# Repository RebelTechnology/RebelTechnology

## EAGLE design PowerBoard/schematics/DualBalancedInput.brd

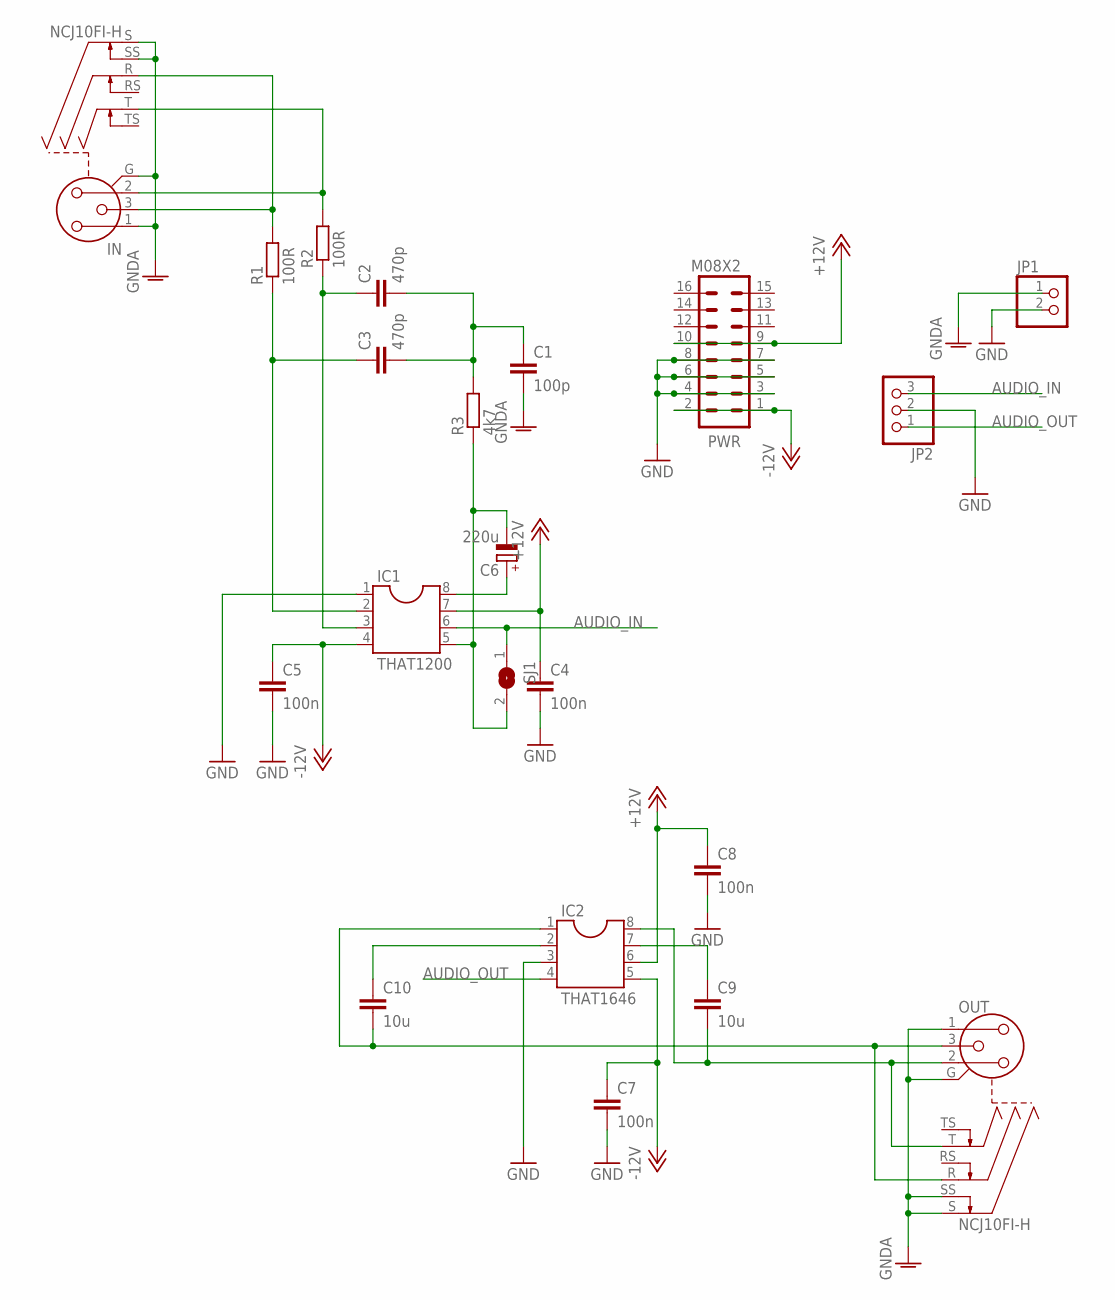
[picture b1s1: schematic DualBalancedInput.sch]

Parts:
C1: 100p; C050-025X075
C2, C3: 470p; C050-025X075
C4, C5, C7, C8: 100n; C050-025X075
C6: 220u; E5-8,5
C9, C10: 10u; C050-025X075
IC1: THAT1200; DIL08
IC2: THAT1646; DIL08
IN: NCJ10FI-H
JP1: PINHD-1X2; 1X02
JP2: PINHD-1X3; 1X03
OUT: NCJ10FI-H
PWR: M08X2; 2X8
R1, R2: 100R; 0207/7
R3: 4k7; 0207/7
SJ1: SJW

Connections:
+12V: C4.1, C8.1, IC1.7, IC2.6, PWR.9, PWR.10
-12V: C5.1, C7.1, IC1.4, IC2.5, PWR.1, PWR.2
AUDIO_IN: IC1.6, JP2.3, SJ1.1
AUDIO_OUT: IC2.4, JP2.1
GND: C4.2, C5.2, C7.2, C8.2, IC1.1, IC2.3, JP1.2, JP2.2, PWR.3, PWR.4, PWR.5, PWR.6, PWR.7, PWR.8
GNDA: C1.2, IN.1, IN.G, IN.S, IN.SS, JP1.1, OUT.1, OUT.G, OUT.S, OUT.SS
unnamed: C3.1, IC1.2, R1.1
unnamed: IN.3, IN.R, R1.2
unnamed: C2.1, IC1.3, R2.1
unnamed: IN.2, IN.T, R2.2
unnamed: C6.-, IC1.5, R3.1, SJ1.2
unnamed: C1.1, C2.2, C3.2, R3.2
unnamed: C9.1, IC2.7
unnamed: C10.1, IC2.2
unnamed: C6.+, IC1.8
unnamed: C9.2, IC2.8, OUT.2, OUT.T
unnamed: C10.2, IC2.1, OUT.3, OUT.R

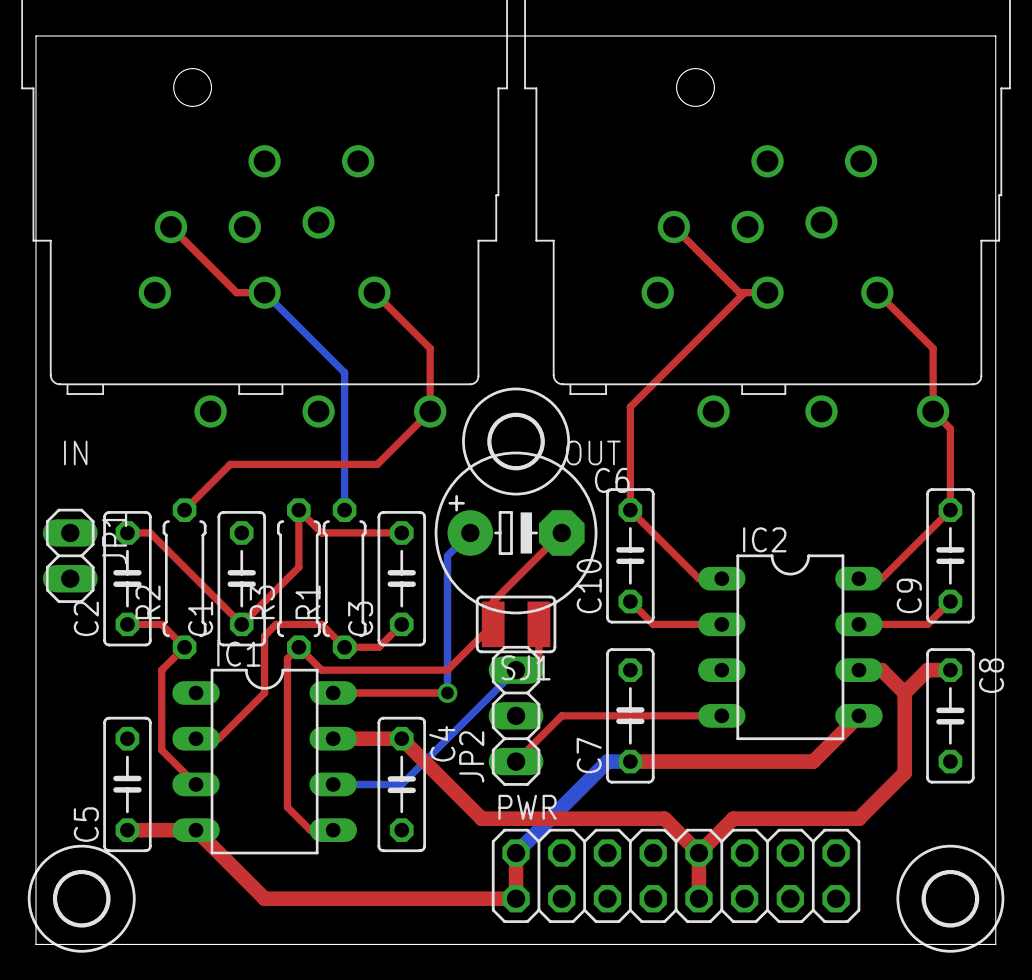
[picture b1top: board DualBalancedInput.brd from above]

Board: 2 copper layers, 53.3 x 50.5 mm, 24 parts (0 on the bottom side), 17 nets.

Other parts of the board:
U$1, U$2, U$3: 2,8

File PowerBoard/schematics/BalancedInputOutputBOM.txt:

Partlist exported from D:/Drive/Work/Rebel/ProjectFiles/RebelTechnology/PowerBoard/schematics/BalancedInputOutput.sch at 13/04/2015 14:58:14

Qty Value     Device          Package      Parts          Description                          
2             PINHD-1X2       1X02         JP1, JP3       PIN HEADER                           
1             PINHD-1X3       1X03         JP2            PIN HEADER                           
1             SJW             SJW          SJ1            SMD solder JUMPER                    
2   100R      R-EU_0207/7     0207/7       R1, R2         RESISTOR, European symbol            
4   100n      C-EU050-025X075 C050-025X075 C4, C5, C7, C8 CAPACITOR, European symbol           
1   100p      C-EU050-025X075 C050-025X075 C1             CAPACITOR, European symbol           
2   10u       C-EU050-025X075 C050-025X075 C9, C10        CAPACITOR, European symbol           
1   220u      CPOL-EUE5-8.5   E5-8,5       C6             POLARIZED CAPACITOR, European symbol 
2   470p      C-EU050-025X075 C050-025X075 C2, C3         CAPACITOR, European symbol           
1   4k7       R-EU_0207/7     0207/7       R3             RESISTOR, European symbol            
1   M08X2     M08X2           2X8          PWR                                                 
2   NCJ10FI-H NCJ10FI-H       NCJ10FI-H    IN, OUT        Neutrik Audio Connector XLR SERIES   
1   THAT1200  DIL8            DIL08        IC1            Dual In Line / Socket                
1   THAT1646  DIL8            DIL08        IC2            Dual In Line / Socket

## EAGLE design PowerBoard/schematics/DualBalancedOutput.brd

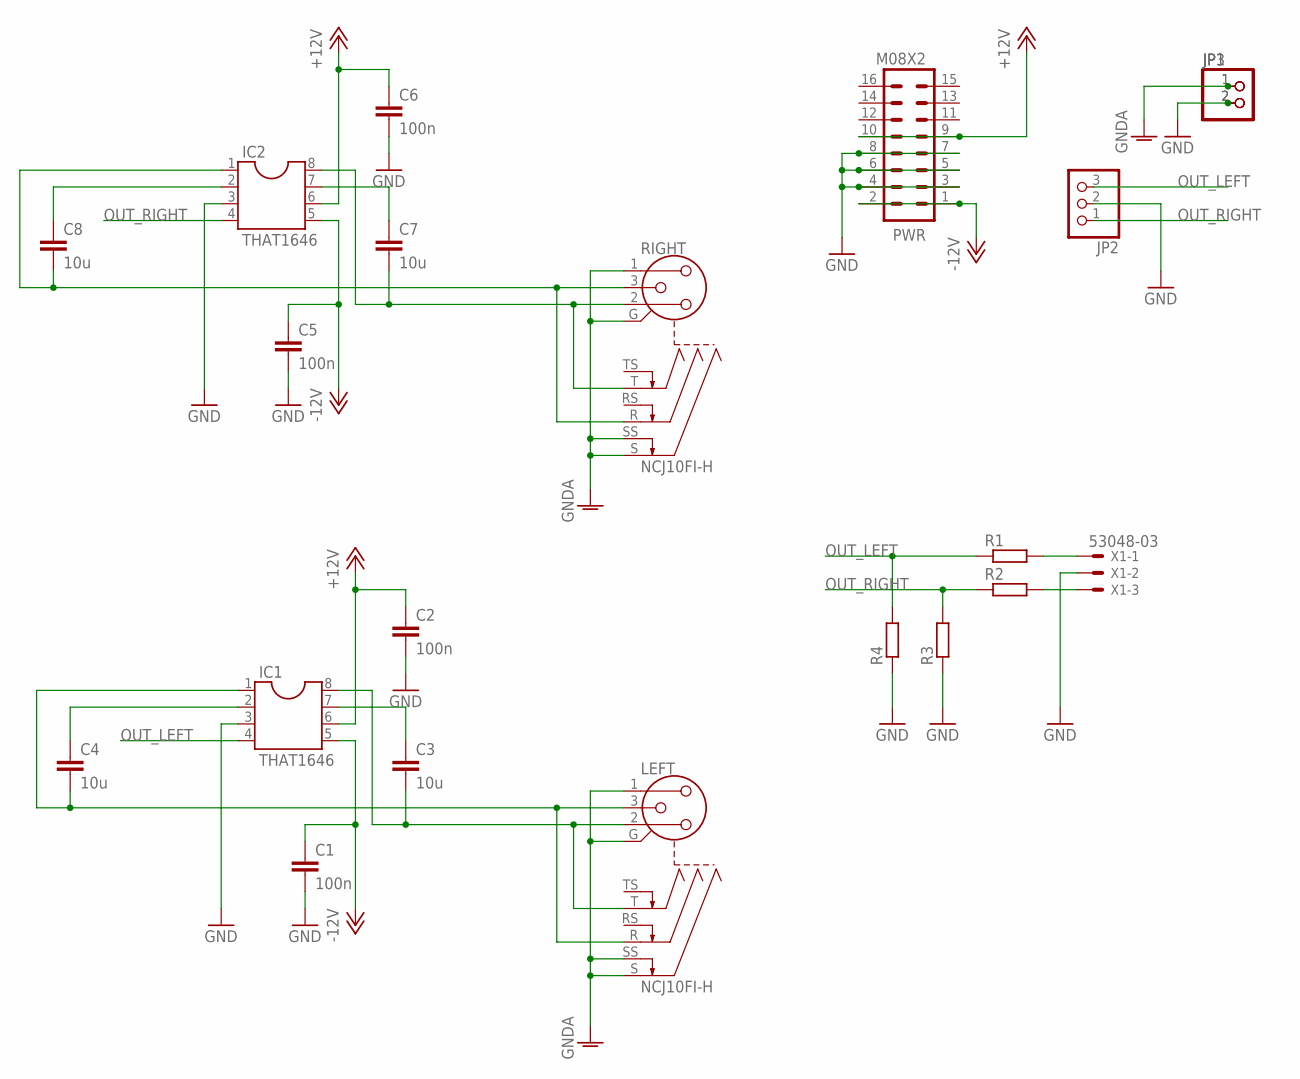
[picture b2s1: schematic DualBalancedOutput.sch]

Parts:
C1, C2, C5, C6: 100n; C050-025X075
C3, C4, C7, C8: 10u; C050-025X075
IC1, IC2: THAT1646; DIL08
JP1, JP3: PINHD-1X2; 1X02
JP2: PINHD-1X3; 1X03
LEFT: NCJ10FI-H
PWR: M08X2; 2X8
R1, R2, R3, R4: R-EU_0207/7; 0207/7
RIGHT: NCJ10FI-H
X1: 53048-03

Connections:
+12V: C2.1, C6.1, IC1.6, IC2.6, PWR.9, PWR.10
-12V: C1.1, C5.1, IC1.5, IC2.5, PWR.1, PWR.2
GND: C1.2, C2.2, C5.2, C6.2, IC1.3, IC2.3, JP1.2, JP2.2, JP3.2, PWR.3, PWR.4, PWR.5, PWR.6, PWR.7, PWR.8, R3.1, R4.1, X1.2
GNDA: JP1.1, JP3.1, LEFT.1, LEFT.G, LEFT.S, LEFT.SS, RIGHT.1, RIGHT.G, RIGHT.S, RIGHT.SS
unnamed: C3.2, IC1.8, LEFT.2, LEFT.T
unnamed: C4.2, IC1.1, LEFT.3, LEFT.R
unnamed: C3.1, IC1.7
unnamed: C4.1, IC1.2
unnamed: R2.2, X1.3
unnamed: C7.1, IC2.7
unnamed: R1.2, X1.1
unnamed: C8.1, IC2.2
unnamed: C7.2, IC2.8, RIGHT.2, RIGHT.T
unnamed: C8.2, IC2.1, RIGHT.3, RIGHT.R
OUT_LEFT: IC1.4, JP2.3, R1.1, R4.2
OUT_RIGHT: IC2.4, JP2.1, R2.1, R3.2

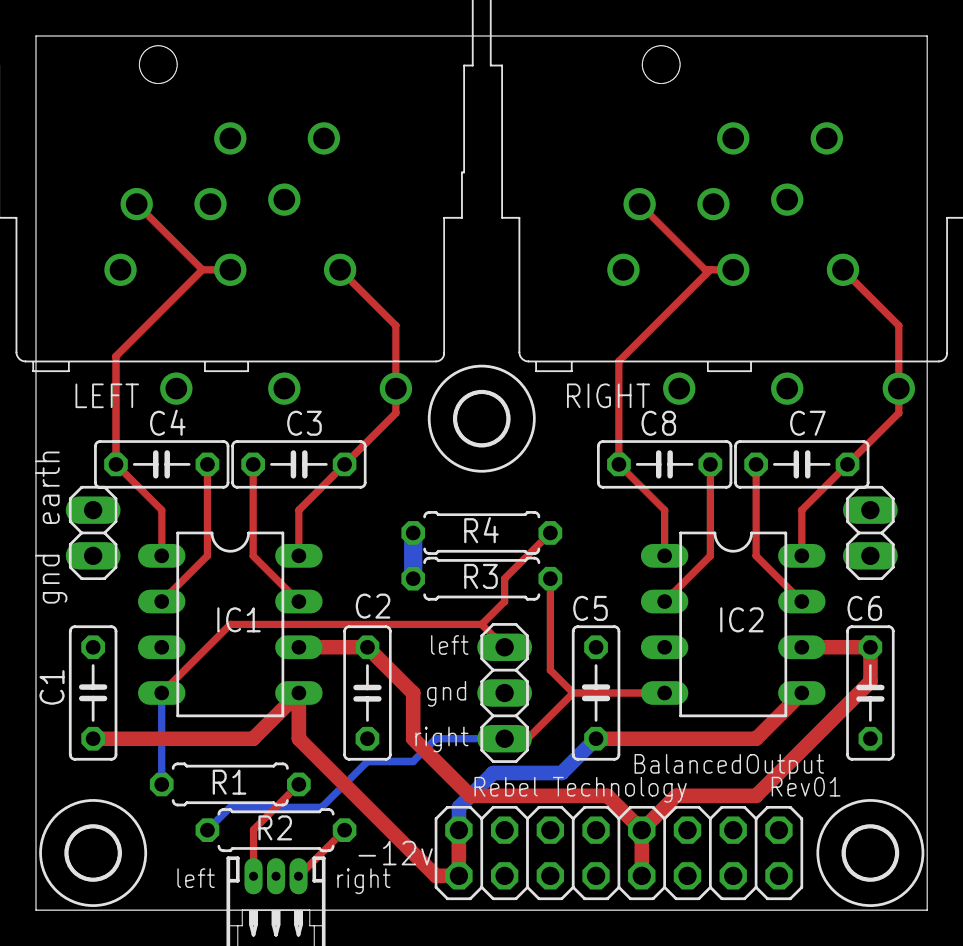
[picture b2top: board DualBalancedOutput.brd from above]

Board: 2 copper layers, 49.5 x 48.6 mm, 24 parts (0 on the bottom side), 16 nets.

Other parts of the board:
U$1, U$2, U$3: 2,8

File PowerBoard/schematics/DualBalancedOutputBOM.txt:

Partlist exported from D:/Drive/Work/Rebel/ProjectFiles/RebelTechnology/PowerBoard/schematics/DualBalancedOutput.sch at 13/04/2015 15:21:52

Qty Value     Device          Package      Parts          Description                        
2             PINHD-1X2       1X02         JP1, JP3       PIN HEADER                         
1             PINHD-1X3       1X03         JP2            PIN HEADER                         
4             R-EU_0207/7     0207/7       R1, R2, R3, R4 RESISTOR, European symbol          
4   100n      C-EU050-025X075 C050-025X075 C1, C2, C5, C6 CAPACITOR, European symbol         
4   10u       C-EU050-025X075 C050-025X075 C3, C4, C7, C8 CAPACITOR, European symbol         
1   53048-03  53048-03        53048-03     X1             CONNECTOR                          
1   M08X2     M08X2           2X8          PWR                                               
2   NCJ10FI-H NCJ10FI-H       NCJ10FI-H    LEFT, RIGHT    Neutrik Audio Connector XLR SERIES 
2   THAT1646  DIL8            DIL08        IC1, IC2       Dual In Line / Socket

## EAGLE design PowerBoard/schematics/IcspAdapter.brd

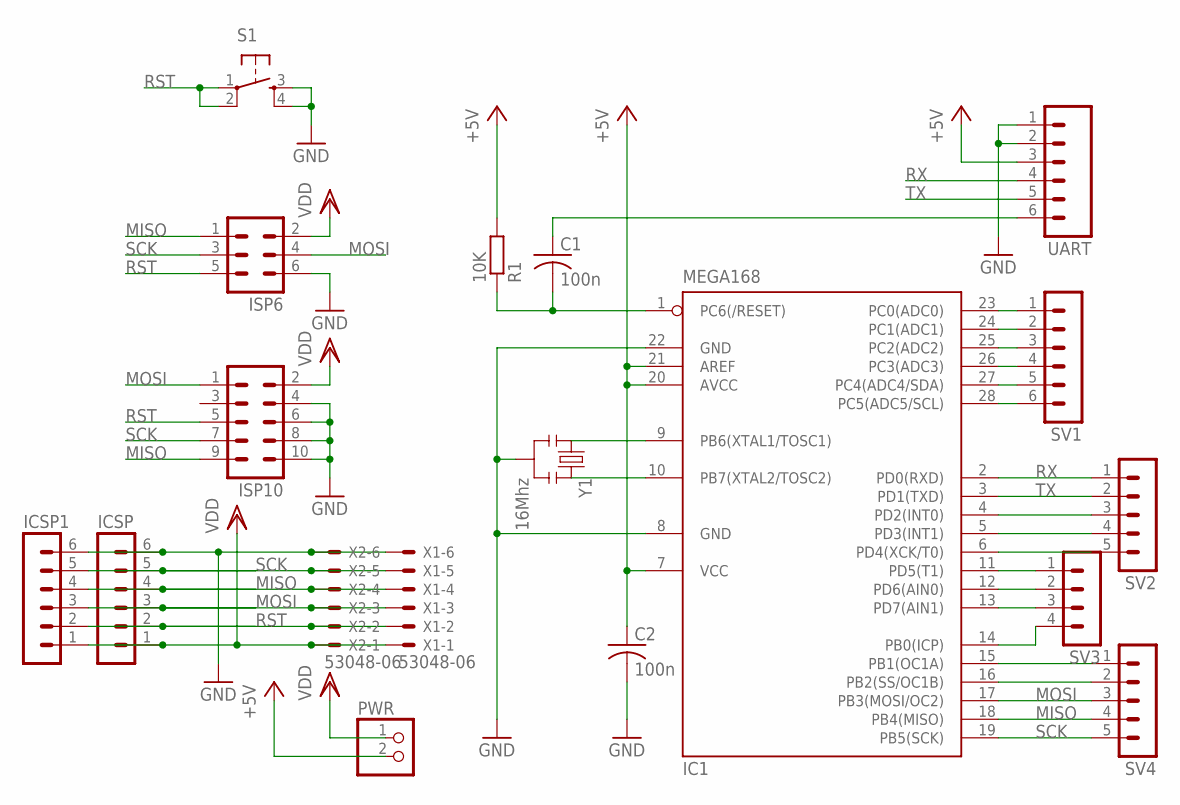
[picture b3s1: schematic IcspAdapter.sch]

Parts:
C1, C2: 100n; C050-024X044
IC1: MEGA168; DIL28-3
ICSP, ICSP1: MA06-1
ISP6: MA03-2
ISP10: MA05-2
PWR: PINHD-1X2; 1X02
R1: 10K; 0204/7
S1: TAC_SWITCHPTH; TACTILE-PTH
SV1: MA06-1
SV2, SV4: MA05-1
SV3: MA04-1
UART: M06SIP; 1X06
X1, X2: 53048-06
Y1: 16Mhz; RESONATOR-PTH

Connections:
+5V: C2.1, IC1.7 (VCC), IC1.20 (AVCC), IC1.21 (AREF), PWR.2, R1.2, UART.3
GND: C2.2, IC1.8 (GND), IC1.22 (GND), ICSP.6, ICSP1.6, ISP6.6, ISP10.4, ISP10.6, ISP10.8, ISP10.10, S1.3, S1.4, UART.1, UART.2, X1.6, X2.6, Y1.2
MISO: IC1.18 (PB4(MISO)), ICSP.4, ICSP1.4, ISP6.1, ISP10.9, SV4.4, X1.4, X2.4
MOSI: IC1.17 (PB3(MOSI/OC2)), ICSP.3, ICSP1.3, ISP6.4, ISP10.1, SV4.3, X1.3, X2.3
unnamed: IC1.23 (PC0(ADC0)), SV1.1
unnamed: IC1.24 (PC1(ADC1)), SV1.2
unnamed: IC1.25 (PC2(ADC2)), SV1.3
unnamed: IC1.26 (PC3(ADC3)), SV1.4
unnamed: IC1.16 (PB2(SS/OC1B)), SV4.2
unnamed: IC1.9 (PB6(XTAL1/TOSC1)), Y1.1
unnamed: IC1.10 (PB7(XTAL2/TOSC2)), Y1.3
unnamed: IC1.27 (PC4(ADC4/SDA)), SV1.5
unnamed: IC1.28 (PC5(ADC5/SCL)), SV1.6
unnamed: IC1.4 (PD2(INT0)), SV2.3
unnamed: IC1.5 (PD3(INT1)), SV2.4
unnamed: IC1.6 (PD4(XCK/T0)), SV2.5
unnamed: IC1.11 (PD5(T1)), SV3.1
unnamed: IC1.12 (PD6(AIN0)), SV3.2
unnamed: IC1.13 (PD7(AIN1)), SV3.3
unnamed: IC1.14 (PB0(ICP)), SV3.4
unnamed: IC1.15 (PB1(OC1A)), SV4.1
RX: IC1.2 (PD0(RXD)), SV2.1, UART.4
SCK: IC1.19 (PB5(SCK)), ICSP.5, ICSP1.5, ISP6.3, ISP10.7, SV4.5, X1.5, X2.5
TX: IC1.3 (PD1(TXD)), SV2.2, UART.5
VDD: ICSP.1, ICSP1.1, ISP6.2, ISP10.2, PWR.1, X1.1, X2.1

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
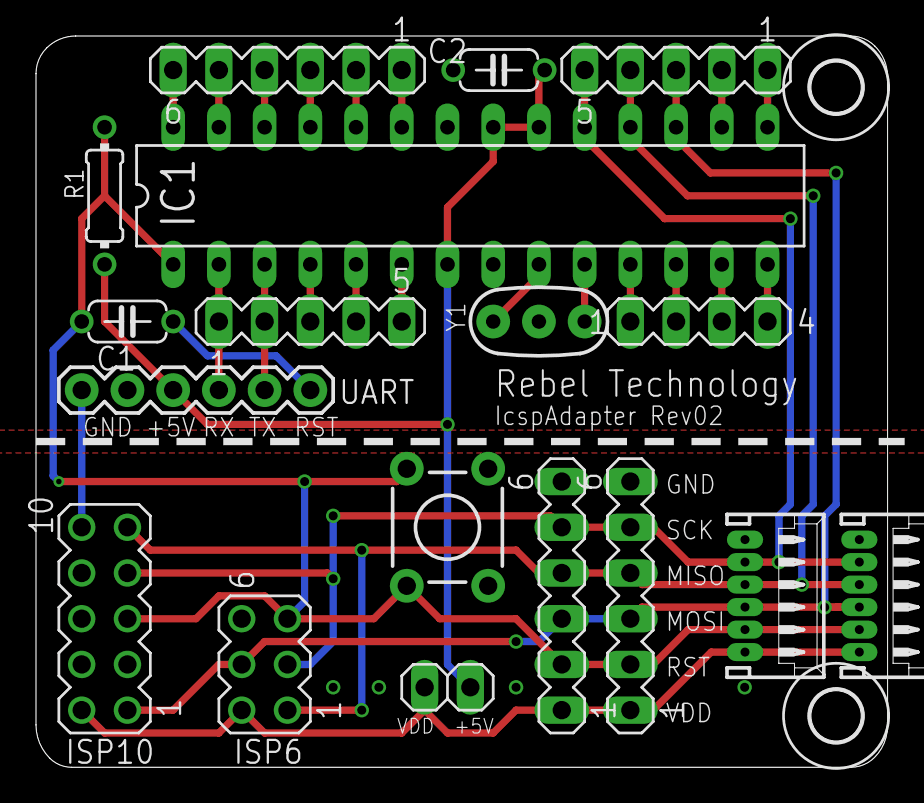
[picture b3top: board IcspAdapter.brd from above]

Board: 2 copper layers, 47.3 x 40.6 mm, 20 parts (0 on the bottom side), 27 nets.

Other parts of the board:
U$1, U$5: 2,8

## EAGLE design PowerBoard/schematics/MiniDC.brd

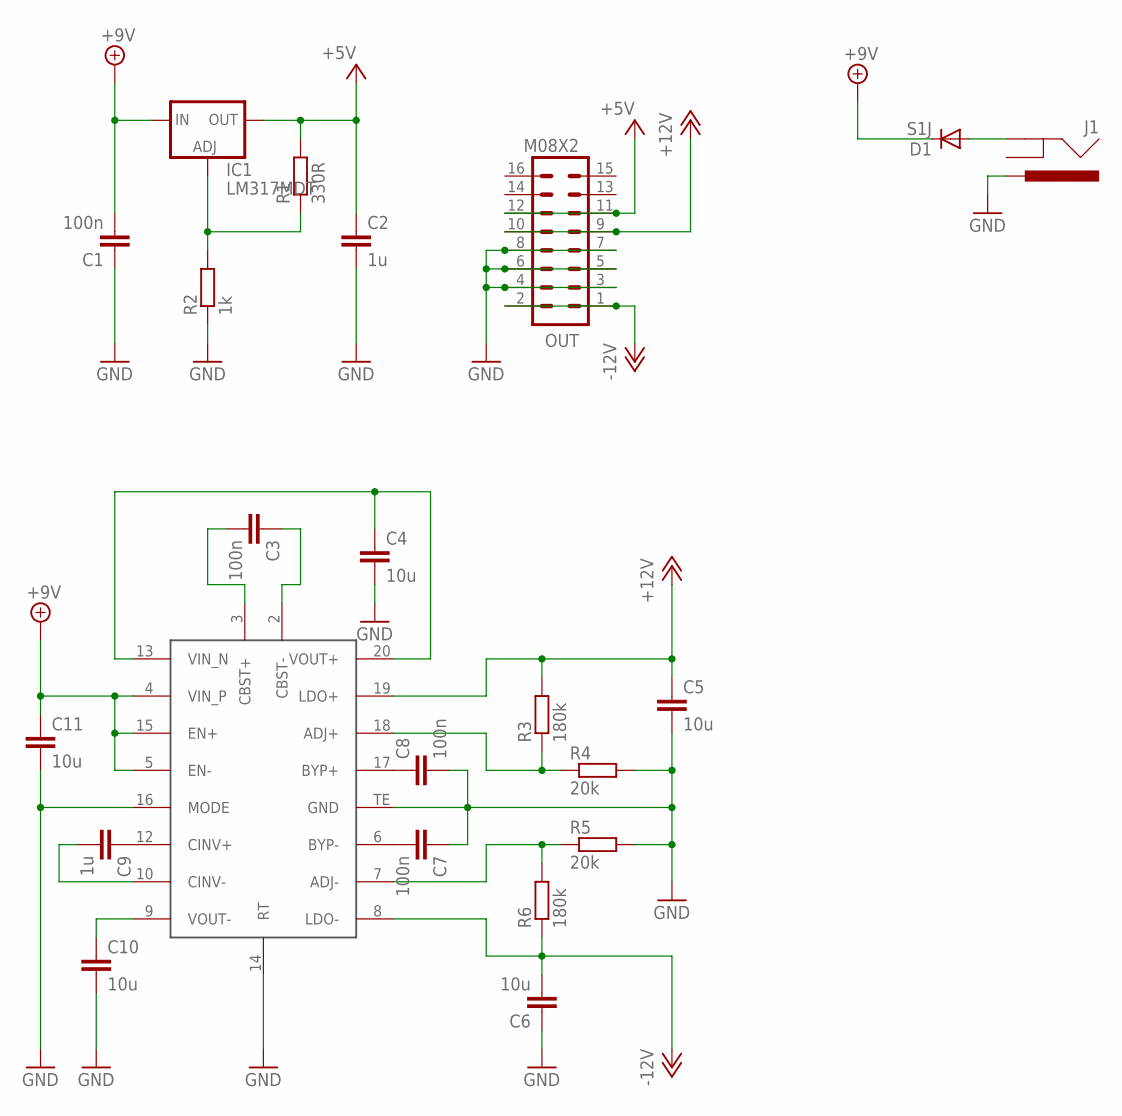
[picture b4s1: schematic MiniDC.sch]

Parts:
C1, C3, C7, C8: 100n; C0603
C2: 1u; C1206K
C4, C5, C6, C10, C11: 10u; C1206K
C9: 1u; C1206
D1: S1J; SMA-DIODE
IC1: LM317MDT; DPACK
IC2: LTC3265; TSSOP20-TE
J1: POWER_JACKPTH; POWER_JACK_PTH
OUT: M08X2; 2X8
R1: 330R; 0603
R2: 1k; 0603
R3, R6: 180k; 0603
R4, R5: 20k; 0603

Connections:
+5V: C2.1, IC1.4 (OUT), OUT.11, OUT.12, R1.2
+9V: C1.2, C11.1, D1.C, IC1.3 (IN), IC2.4 (VIN_P), IC2.5 (EN-), IC2.15 (EN+)
+12V: C5.1, IC2.19 (LDO+), OUT.9, OUT.10, R3.2
-12V: C6.2, IC2.8 (LDO-), OUT.1, OUT.2, R6.1
GND: C1.1, C2.2, C4.2, C5.2, C6.1, C7.1, C8.2, C10.2, C11.2, IC2.14 (RT), IC2.16 (MODE), IC2.TE (GND), J1.PWR, OUT.3, OUT.4, OUT.5, OUT.6, OUT.7, OUT.8, R2.1, R4.2, R5.2
unnamed: IC1.1 (ADJ), R1.1, R2.2
unnamed: C4.1, IC2.13 (VIN_N), IC2.20 (VOUT+)
unnamed: C3.1, IC2.2 (CBST-)
unnamed: C3.2, IC2.3 (CBST+)
unnamed: C7.2, IC2.6 (BYP-)
unnamed: IC2.18 (ADJ+), R3.1, R4.1
unnamed: C8.1, IC2.17 (BYP+)
unnamed: C9.1, IC2.12 (CINV+)
unnamed: IC2.7 (ADJ-), R5.1, R6.2
unnamed: C10.1, IC2.9 (VOUT-)
unnamed: C9.2, IC2.10 (CINV-)
unnamed: D1.A, J1.GND

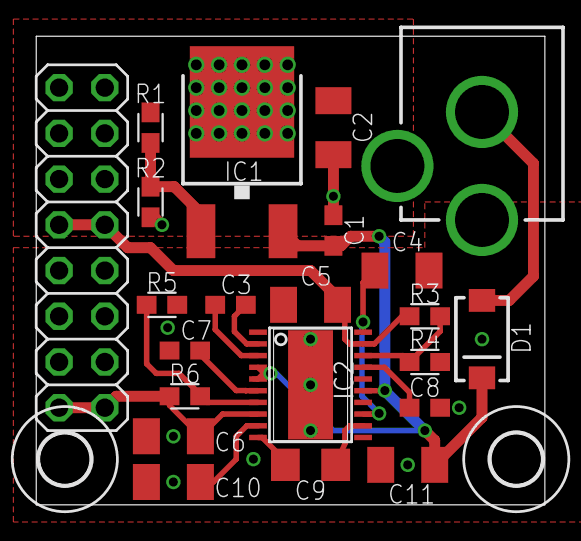
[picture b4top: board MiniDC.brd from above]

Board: 2 copper layers, 28.3 x 26.0 mm, 24 parts (0 on the bottom side), 17 nets.

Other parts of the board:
U$2, U$3: 2,8

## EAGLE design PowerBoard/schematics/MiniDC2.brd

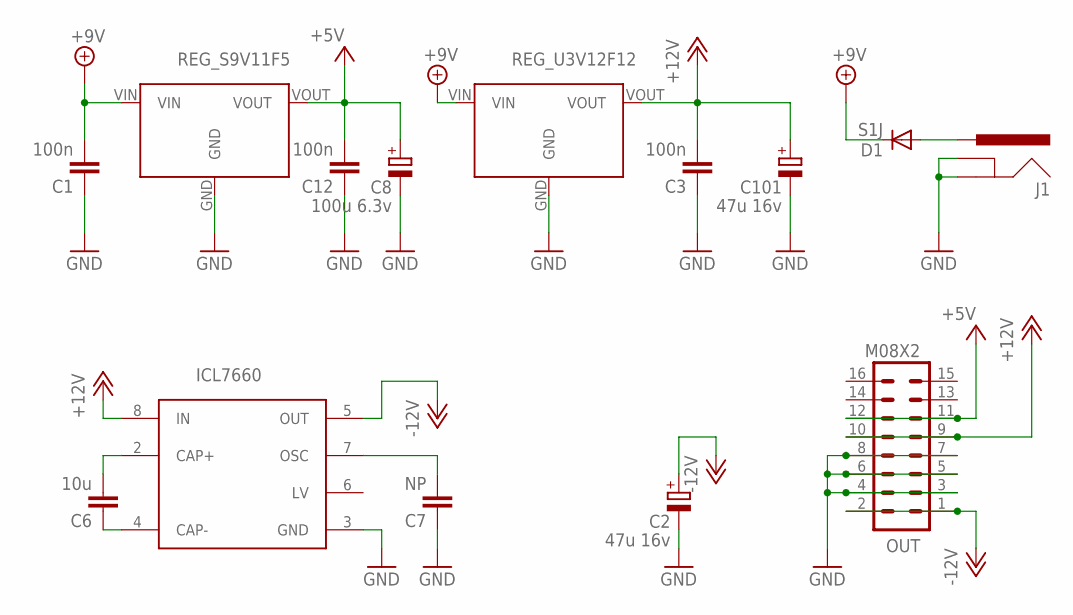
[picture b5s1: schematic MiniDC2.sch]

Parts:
C1, C3, C12: 100n; C0603
C2, C101: 47u 16v; PANASONIC_B
C6: 10u; C1206
C7: NP; C0603
C8: 100u 6.3v; PANASONIC_B
D1: S1J; SMA-DIODE
J1: POWER_JACKPTH; POWER_JACK_PTH
OUT: M08X2; 2X8
U1: REG_S9V11F5
U2: REG_U3V12F12; REG_S9V11F5
U3: ICL7660; SOIC8

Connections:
+5V: C8.+, C12.2, OUT.11, OUT.12, U1.VOUT
+9V: C1.2, D1.C, U1.VIN, U2.VIN
+12V: C3.2, C101.+, OUT.9, OUT.10, U2.VOUT, U3.8 (IN)
-12V: C2.+, OUT.1, OUT.2, U3.5 (OUT)
GND: C1.1, C2.-, C3.1, C7.1, C8.-, C12.1, C101.-, J1.GND, J1.GNDBREAK, OUT.3, OUT.4, OUT.5, OUT.6, OUT.7, OUT.8, U1.GND, U2.GND, U3.3 (GND)
unnamed: D1.A, J1.PWR
unnamed: C6.1, U3.4 (CAP-)
unnamed: C6.2, U3.2 (CAP+)
unnamed: C7.2, U3.7 (OSC)

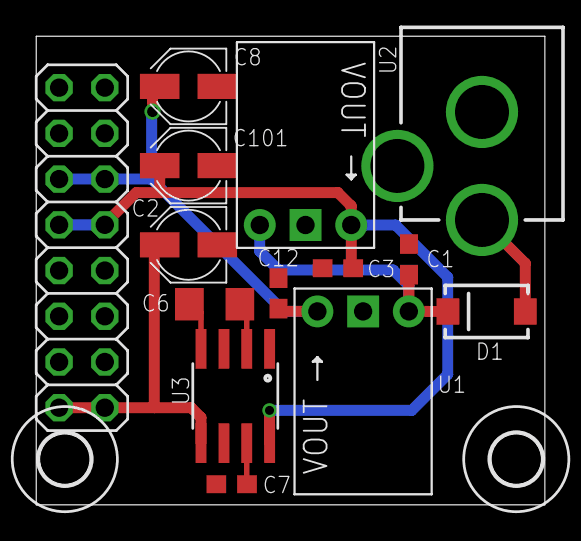
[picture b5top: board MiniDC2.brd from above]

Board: 2 copper layers, 28.3 x 26.0 mm, 16 parts (0 on the bottom side), 9 nets.

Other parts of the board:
U$2, U$3: 2,8

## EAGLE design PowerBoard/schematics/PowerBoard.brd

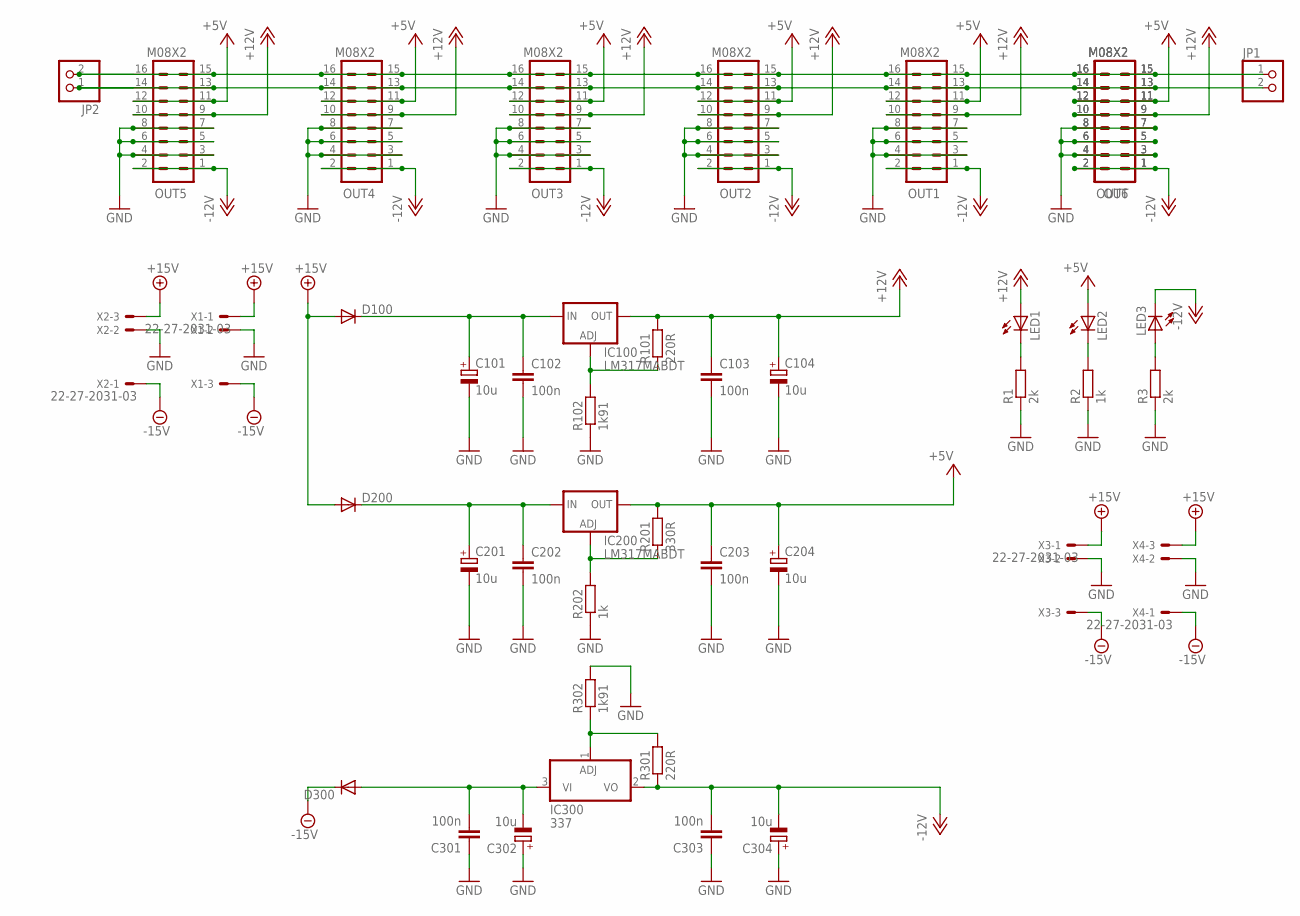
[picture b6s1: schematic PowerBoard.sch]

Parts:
C101, C104, C201, C204, C302, C304: 10u; 153CLV-0810
C102, C103, C202, C203, C301, C303: 100n; C0603
D100, D200, D300: DIODESMA; SMA-DIODE
IC100, IC200: LM317MABDT; DPACK
IC300: 337; TO252
JP1, JP2: PINHD-1X2; 1X02
LED1, LED2, LED3: LEDCHIPLED_1206; CHIPLED_1206
OUT, OUT1, OUT2, OUT3, OUT4, OUT5, OUT6: M08X2; 2X8
R1, R3: 2k; 0603
R2, R202: 1k; 0603
R101, R301: 220R; 0603
R102, R302: 1k91; 0603
R201: 330R; 0603
X1, X2, X3, X4: 22-27-2031-03; 6410-03

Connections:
+5V: C203.1, C204.+, IC200.4 (OUT), LED2.A, OUT.11, OUT.12, OUT1.11, OUT1.12, OUT2.11, OUT2.12, OUT3.11, OUT3.12, OUT4.11, OUT4.12, OUT5.11, OUT5.12, OUT6.11, OUT6.12, R201.2
+12V: C103.1, C104.+, IC100.4 (OUT), LED1.A, OUT.9, OUT.10, OUT1.9, OUT1.10, OUT2.9, OUT2.10, OUT3.9, OUT3.10, OUT4.9, OUT4.10, OUT5.9, OUT5.10, OUT6.9, OUT6.10, R101.2
+15V: D100.A, D200.A, X1.1, X2.3, X3.1, X4.3
-12V: C303.2, C304.-, IC300.2 (VO), LED3.C, OUT.1, OUT.2, OUT1.1, OUT1.2, OUT2.1, OUT2.2, OUT3.1, OUT3.2, OUT4.1, OUT4.2, OUT5.1, OUT5.2, OUT6.1, OUT6.2, R301.1
-15V: D300.C, X1.3, X2.1, X3.3, X4.1
GND: C101.-, C102.2, C103.2, C104.-, C201.-, C202.2, C203.2, C204.-, C301.1, C302.+, C303.1, C304.+, OUT.3, OUT.4, OUT.5, OUT.6, OUT.7, OUT.8, OUT1.3, OUT1.4, OUT1.5, OUT1.6, OUT1.7, OUT1.8, OUT2.3, OUT2.4, OUT2.5, OUT2.6, OUT2.7, OUT2.8, OUT3.3, OUT3.4, OUT3.5, OUT3.6, OUT3.7, OUT3.8, OUT4.3, OUT4.4, OUT4.5, OUT4.6, OUT4.7, OUT4.8, OUT5.3, OUT5.4, OUT5.5, OUT5.6, OUT5.7, OUT5.8, OUT6.3, OUT6.4, OUT6.5, OUT6.6, OUT6.7, OUT6.8, R1.1, R2.1, R3.1, R102.1, R202.1, R302.2, X1.2, X2.2, X3.2, X4.2
unnamed: LED1.C, R1.2
unnamed: LED2.C, R2.2
unnamed: IC100.1 (ADJ), R101.1, R102.2
unnamed: IC200.1 (ADJ), R201.1, R202.2
unnamed: IC300.1 (ADJ), R301.2, R302.1
unnamed: C301.2, C302.-, D300.A, IC300.3 (VI)
unnamed: C201.+, C202.1, D200.C, IC200.3 (IN)
unnamed: C101.+, C102.1, D100.C, IC100.3 (IN)
unnamed: LED3.A, R3.2
unnamed: JP1.2, JP2.1, OUT.13, OUT.14, OUT1.13, OUT1.14, OUT2.13, OUT2.14, OUT3.13, OUT3.14, OUT4.13, OUT4.14, OUT5.13, OUT5.14, OUT6.13, OUT6.14
unnamed: JP1.1, JP2.2, OUT.15, OUT.16, OUT1.15, OUT1.16, OUT2.15, OUT2.16, OUT3.15, OUT3.16, OUT4.15, OUT4.16, OUT5.15, OUT5.16, OUT6.15, OUT6.16

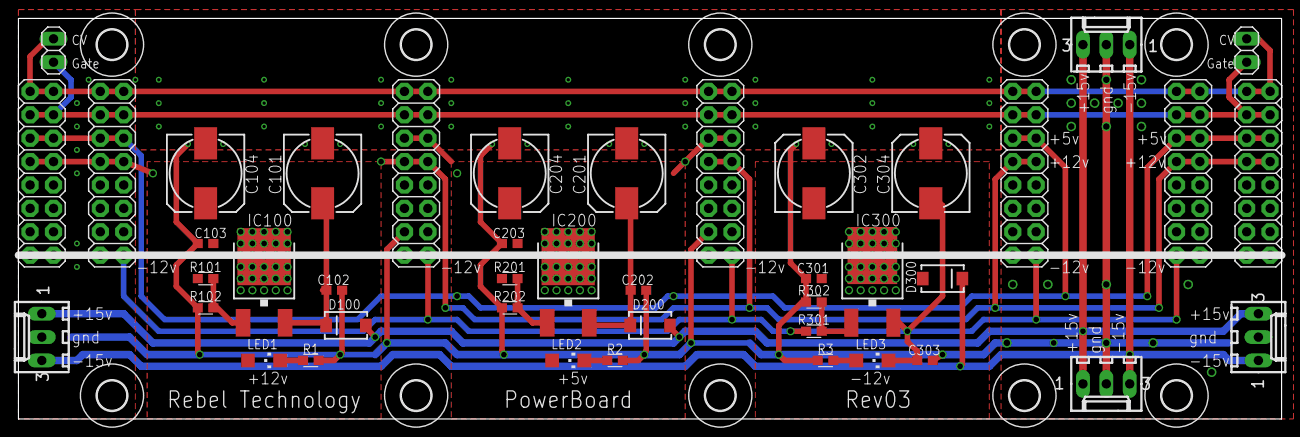
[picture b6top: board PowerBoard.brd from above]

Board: 2 copper layers, 137.1 x 43.5 mm, 53 parts (0 on the bottom side), 17 nets.

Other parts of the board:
U$1, U$2, U$3, U$4, U$5, U$6, U$7, U$8, U$12, U$13: 3,2

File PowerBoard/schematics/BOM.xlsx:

Qty | Value | Device | Parts | Description
3 |  | DIODESMA | D100, D200, D300 | Diode
3 |  | LEDCHIPLED_1206 | LED1, LED2, LED3 | LED
3 | 100n | C-EUC0603 | C102, C202, C301 | CAPACITOR, European symbol
6 | 10u | CPOL-EU153CLV-0810 | C101, C104, C201, C204, C302, C304 | POLARIZED CAPACITOR, European symbol
4 | 1k | R-EU_0603 | R2, R202 | RESISTOR, European symbol
3 | 1u | C-EUC0603 | C103, C203, C303 | CAPACITOR, European symbol
4 | 22-27-2031-03 | 22-27-2031-03 | X1, X2, X3, X4 | CONNECTOR
2 | 220R | R-EU_0603 | R101, R301 | RESISTOR, European symbol
2 | 1.91k | R-EU_0603 | R102, R302 | RESISTOR, European symbol
1 | 330R | R-EU_0603 | R201 | RESISTOR, European symbol
1 | LM337 | TO252 | IC300 | Negative VOLTAGE REGULATOR
2 | LM317MABDT | LM317MABDT | IC100, IC200 | 500 mA Adjustable Output Positive Voltage Regulator
6 | M08X2 | M08X2 | OUT, OUT1, OUT2, OUT3, OUT4, OUT5
6 | dnp | CPOL-EUE5-8.5 | C100, C105, C200, C205, C300, C305 | POLARIZED CAPACITOR, European symbol
2 | 2k | R-EU_0603 | R1, R3 | RESISTOR, European symbol

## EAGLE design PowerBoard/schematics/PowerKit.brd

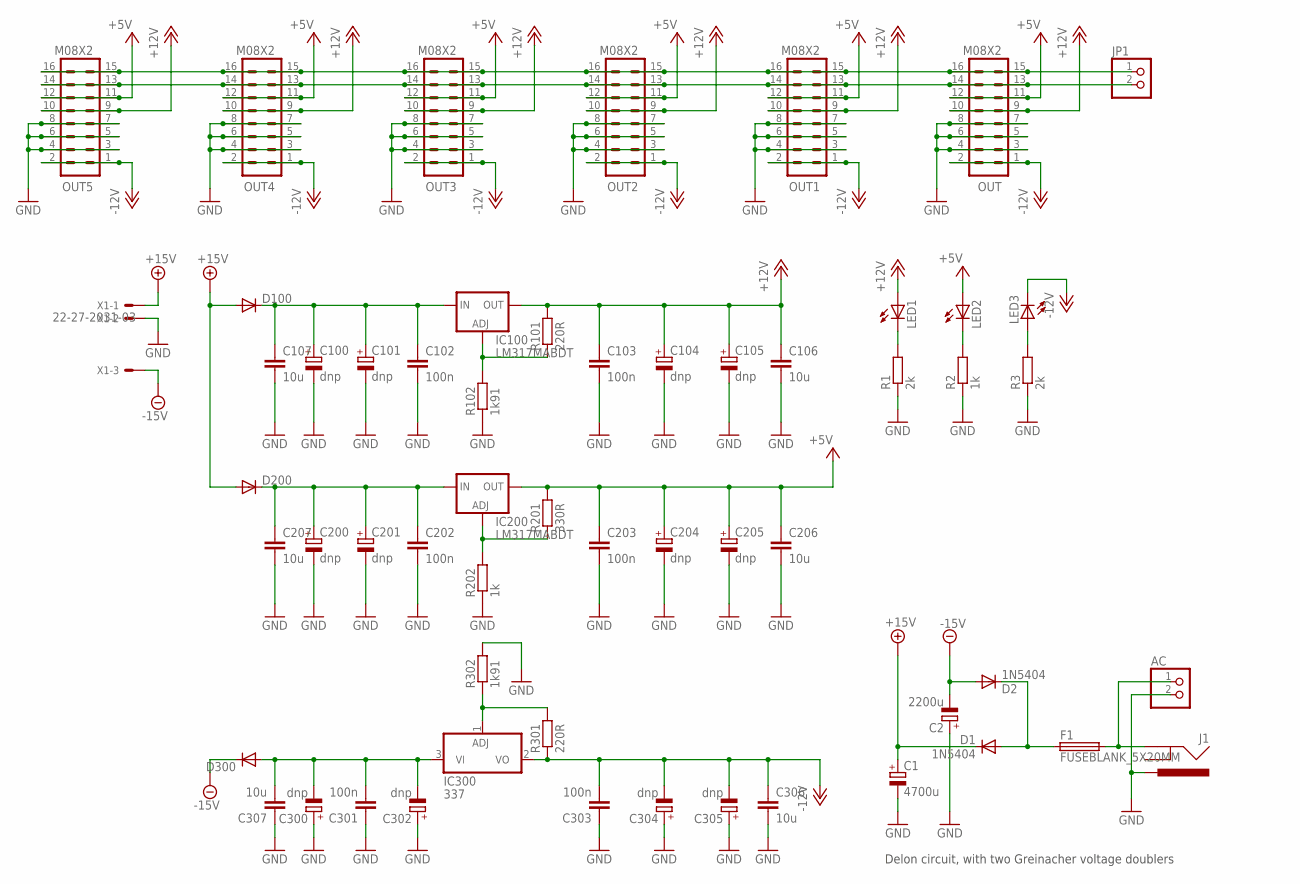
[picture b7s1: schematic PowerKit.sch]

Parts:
AC: PINHD-1X2; 1X02
C1: 4700u; E7,5-18
C2: 2200u; E7,5-18
C100, C105, C200, C205, C300, C305: dnp; E5-8,5
C101, C104, C201, C204, C302, C304: dnp; 153CLV-0810
C102, C103, C202, C203, C301, C303: 100n; C0603
C106, C107, C206, C207, C306, C307: 10u; C1206
D1, D2: 1N5404; DIODE-1N4001
D100, D200, D300: DIODESMA; SMA-DIODE
F1: FUSEBLANK_5X20MM; FUSE_HOLDER_5X20MM
IC100, IC200: LM317MABDT; DPACK
IC300: 337; TO252
J1: POWER_JACKPTH; POWER_JACK_PTH
JP1: PINHD-1X2; 1X02
LED1, LED2, LED3: LEDCHIPLED_1206; CHIPLED_1206
OUT, OUT1, OUT2, OUT3, OUT4, OUT5: M08X2; 2X8
R1, R3: 2k; 0603
R2, R202: 1k; 0603
R101, R301: 220R; 0603
R102, R302: 1k91; 0603
R201: 330R; 0603
X1: 22-27-2031-03; 6410-03

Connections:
+5V: C203.1, C204.+, C205.+, C206.1, IC200.4 (OUT), LED2.A, OUT.11, OUT.12, OUT1.11, OUT1.12, OUT2.11, OUT2.12, OUT3.11, OUT3.12, OUT4.11, OUT4.12, OUT5.11, OUT5.12, R201.2
+12V: C103.1, C104.+, C105.+, C106.1, IC100.4 (OUT), LED1.A, OUT.9, OUT.10, OUT1.9, OUT1.10, OUT2.9, OUT2.10, OUT3.9, OUT3.10, OUT4.9, OUT4.10, OUT5.9, OUT5.10, R101.2
+15V: C1.+, D1.C, D100.A, D200.A, X1.1
-12V: C303.2, C304.-, C305.-, C306.1, IC300.2 (VO), LED3.C, OUT.1, OUT.2, OUT1.1, OUT1.2, OUT2.1, OUT2.2, OUT3.1, OUT3.2, OUT4.1, OUT4.2, OUT5.1, OUT5.2, R301.1
-15V: C2.-, D2.A, D300.C, X1.3
GND: AC.2, C1.-, C2.+, C100.-, C101.-, C102.2, C103.2, C104.-, C105.-, C106.2, C107.2, C200.-, C201.-, C202.2, C203.2, C204.-, C205.-, C206.2, C207.2, C300.+, C301.1, C302.+, C303.1, C304.+, C305.+, C306.2, C307.1, J1.PWR, OUT.3, OUT.4, OUT.5, OUT.6, OUT.7, OUT.8, OUT1.3, OUT1.4, OUT1.5, OUT1.6, OUT1.7, OUT1.8, OUT2.3, OUT2.4, OUT2.5, OUT2.6, OUT2.7, OUT2.8, OUT3.3, OUT3.4, OUT3.5, OUT3.6, OUT3.7, OUT3.8, OUT4.3, OUT4.4, OUT4.5, OUT4.6, OUT4.7, OUT4.8, OUT5.3, OUT5.4, OUT5.5, OUT5.6, OUT5.7, OUT5.8, R1.1, R2.1, R3.1, R102.1, R202.1, R302.2, X1.2
unnamed: LED1.C, R1.2
unnamed: LED2.C, R2.2
unnamed: IC100.1 (ADJ), R101.1, R102.2
unnamed: IC200.1 (ADJ), R201.1, R202.2
unnamed: IC300.1 (ADJ), R301.2, R302.1
unnamed: C300.-, C301.2, C302.-, C307.2, D300.A, IC300.3 (VI)
unnamed: C200.+, C201.+, C202.1, C207.1, D200.C, IC200.3 (IN)
unnamed: C100.+, C101.+, C102.1, C107.1, D100.C, IC100.3 (IN)
unnamed: LED3.A, R3.2
unnamed: JP1.2, OUT.13, OUT.14, OUT1.13, OUT1.14, OUT2.13, OUT2.14, OUT3.13, OUT3.14, OUT4.13, OUT4.14, OUT5.13, OUT5.14
unnamed: D1.A, D2.C, F1.1
unnamed: JP1.1, OUT.15, OUT.16, OUT1.15, OUT1.16, OUT2.15, OUT2.16, OUT3.15, OUT3.16, OUT4.15, OUT4.16, OUT5.15, OUT5.16
unnamed: AC.1, F1.2, J1.GND

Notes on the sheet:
Delon circuit, with two Greinacher voltage doublers

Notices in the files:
parts and their libraries:
SparkFun: Licensing: CC v3.0 Share-Alike You are welcome to use this library for commercial purposes.
